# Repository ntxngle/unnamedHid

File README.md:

# unnamedHid
## What and Why

A multipurpose HID middleman based on a RP2040. Anything from rubber ducky scripts to word-to-phrase replacements are supported.

After witnessing the beautiful mistakes (happy little accidents?) that Apple's autocorrect creates, I sought to implement the same on my computer.

Eventually I realized what I was making was in fact not autocorrect but a very small and versatile HID injector: thus bearing this project.

Disclaimer: This project is only for educational and legal purpose. Do not attempt to write malicious programs or keyloggers. I am not responsible for reproductions of this project being used with malintent.

## Tuff photos

## How it works

THe entire device is based on the RP2040 MCU. The built-in PHY connects to the host computer (important for USB programming), and the PIO bitbang interface is connected to the slave device.

The practice of using the PIO as a second USB PHY is not an original nor failproof idea. This approach, taken from Adafruit's own implementation on their Feather boards, probably won't get you the USB3.0 speeds, or even 2 reliably. However, for low speed keyboards and even mice, this approach works just fine.

## BOM
|name       |footprint                                 |board name                          |quantity|
|-----------|------------------------------------------|------------------------------------|--------|
|100nF      |C_0402_1005Metric                         |C19,C8,C17,C11,C5,C6,C12,C9,C4,C7,C3|11      |
|1uF        |C_0402_1005Metric                         |C2,C13,C1,C10                       |4       |
|USBLC6-2SC6|SOT-23-6                                  |U6,U7                               |2       |
|AP2112K-3.3|SOT-23-5                                  |U3                                  |1       |
|22uF       |C_0402_1005Metric                         |C18                                 |1       |
|TPS2041B   |SOT-23-5                                  |U5                                  |1       |
|USB_A      |USB3_A_Receptacle_Wuerth_692122030100     |J2                                  |1       |
|R          |R_0402_1005Metric                         |R2,R1                               |2       |
|BOOT       |SW_SPST_TS-1088-xR025                     |SW1                                 |1       |
|1k         |R_0402_1005Metric                         |R7,R3,R4                            |3       |
|15k        |R_0402_1005Metric                         |R9,R8                               |2       |
|RUN        |SW_SPST_TS-1088-xR025                     |SW2                                 |1       |
|10k        |R_0402_1005Metric                         |R6,R5                               |2       |
|USB_A      |USB3_A_Plug_Wuerth_692112030100_Horizontal|J1                                  |1       |
|W25Q32JVSS |SOIC-8_5.3x5.3mm_P1.27mm                  |U4                                  |1       |
|15pF       |C_0402_1005Metric                         |C15,C16                             |2       |
|ABM8-272-T3|Crystal_SMD_3225-4Pin_3.2x2.5mm           |Y1                                  |1       |
|RP2040     |QFN-56-1EP_7x7mm_P0.4mm_EP3.2x3.2mm       |U1                                  |1       |

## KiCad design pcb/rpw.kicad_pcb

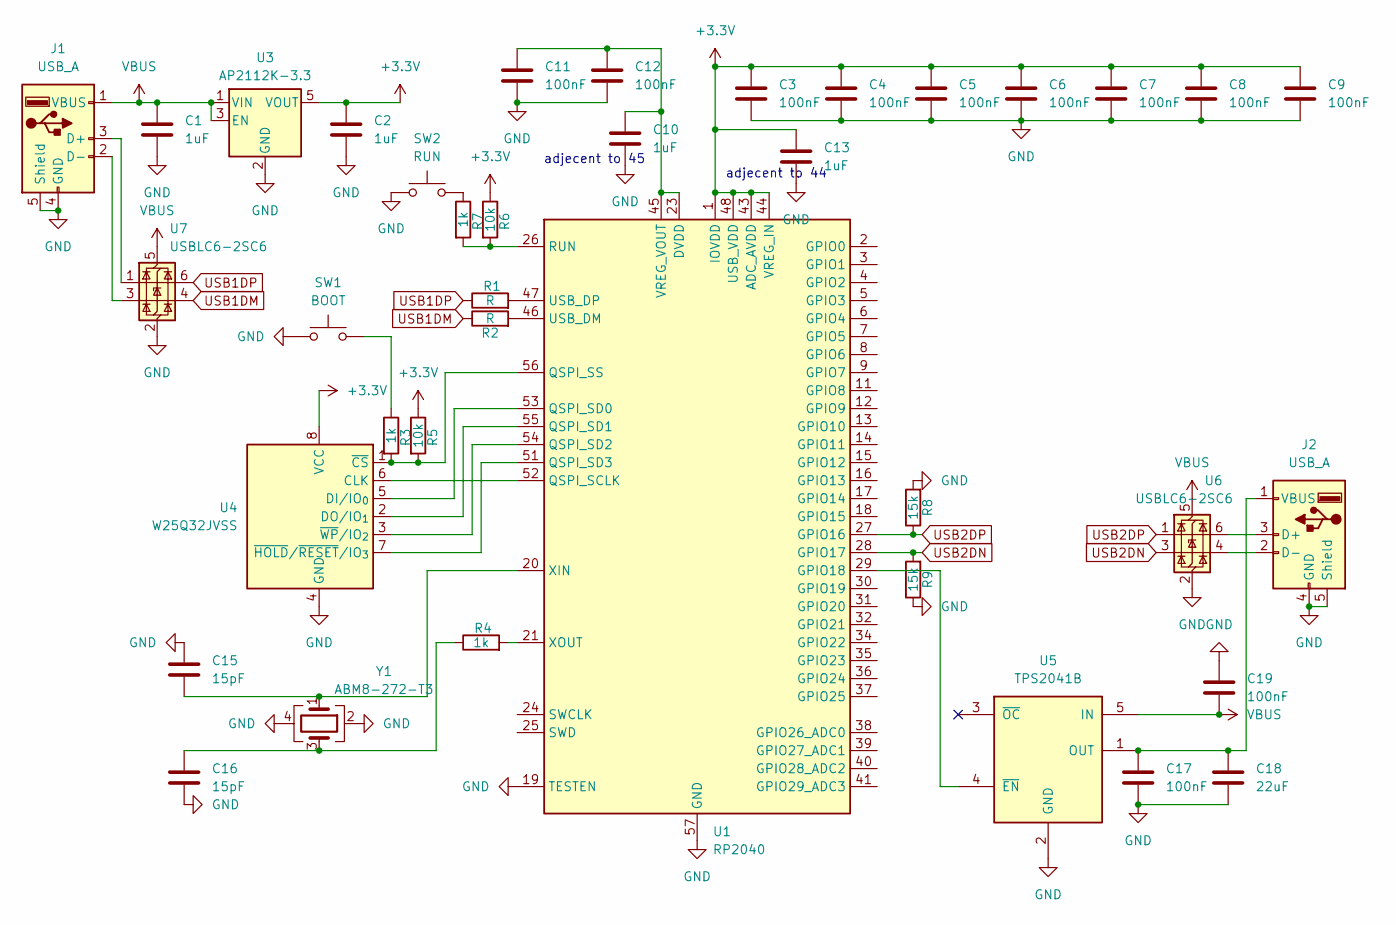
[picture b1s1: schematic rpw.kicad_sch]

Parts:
C1, C2, C10, C13: 1uF; C_0402_1005Metric
C3, C4, C5, C6, C7, C8, C9, C11, C12, C17, C19: 100nF; C_0402_1005Metric
C15, C16: 15pF; C_0402_1005Metric
C18: 22uF; C_0402_1005Metric
J1: USB_A; USB3_A_Plug_Wuerth_692112030100_Horizontal
J2: USB_A; USB3_A_Receptacle_Wuerth_692122030100
R1, R2: R; R_0402_1005Metric
R3, R4, R7: 1k; R_0402_1005Metric
R5, R6: 10k; R_0402_1005Metric
R8, R9: 15k; R_0402_1005Metric
SW1: BOOT; SW_SPST_TS-1088-xR025
SW2: RUN; SW_SPST_TS-1088-xR025
U1: RP2040; QFN-56-1EP_7x7mm_P0.4mm_EP3.2x3.2mm
U3: AP2112K-3.3; SOT-23-5
U4: W25Q32JVSS; SOIC-8_5.3x5.3mm_P1.27mm
U5: TPS2041B; SOT-23-5
U6, U7: USBLC6-2SC6; SOT-23-6
Y1: ABM8-272-T3; Crystal_SMD_3225-4Pin_3.2x2.5mm

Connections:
+3.3V: C2.1, C3.1, C4.1, C5.1, C6.1, C7.1, C8.1, C9.1, C13.1, R5.1, R6.1, U1.1 (IOVDD), U1.10 (IOVDD), U1.22 (IOVDD), U1.33 (IOVDD), U1.42 (IOVDD), U1.43 (ADC_AVDD), U1.44 (VREG_IN), U1.48 (USB_VDD), U1.49 (IOVDD), U3.5 (VOUT), U4.8 (VCC)
GND: C1.2, C2.2, C3.2, C4.2, C5.2, C6.2, C7.2, C8.2, C9.2, C10.2, C11.2, C12.2, C13.2, C15.1, C16.2, C17.2, C18.2, C19.1, J1.4 (GND), J1.5 (Shield), J2.4 (GND), J2.5 (Shield), R8.2, R9.1, SW1.1, SW2.1, U1.19 (TESTEN), U1.57 (GND), U3.2 (GND), U4.4 (GND), U5.2 (GND), U6.2 (GND), U7.2 (GND), Y1.2, Y1.4
unnamed: C16.1, R4.1, Y1.3
unnamed: J1.3 (D+), U7.1 (I/O1)
unnamed: J1.2 (D-), U7.3 (I/O2)
unnamed: J2.3 (D+), U6.6 (I/O1)
unnamed: J2.2 (D-), U6.4 (I/O2)
unnamed: C17.1, C18.1, J2.1 (VBUS), U5.1 (OUT)
unnamed: R3.1, SW1.2
unnamed: R7.1, SW2.2
unnamed: U1.29 (GPIO18), U5.4 (~EN)
unnamed: U1.52 (QSPI_SCLK), U4.6 (CLK)
unnamed: U1.53 (QSPI_SD0), U4.5 (DI/IO_{0})
unnamed: U1.55 (QSPI_SD1), U4.2 (DO/IO_{1})
unnamed: U1.54 (QSPI_SD2), U4.3 (~WP/IO_{2})
unnamed: U1.51 (QSPI_SD3), U4.7 (~HOLD/~RESET/IO_{3})
unnamed: R3.2, R5.2, U1.56 (QSPI_SS), U4.1 (~CS)
unnamed: R6.2, R7.2, U1.26 (RUN)
unnamed: R2.2, U1.46 (USB_DM)
unnamed: R1.2, U1.47 (USB_DP)
unnamed: C10.1, C11.1, C12.1, U1.23 (DVDD), U1.45 (VREG_VOUT), U1.50 (DVDD)
unnamed: C15.2, U1.20 (XIN), Y1.1
unnamed: R4.2, U1.21 (XOUT)
USB1DM: R2.1, U7.4 (I/O2)
USB1DP: R1.1, U7.6 (I/O1)
USB2DN: R9.2, U1.28 (GPIO17), U6.3 (I/O2)
USB2DP: R8.1, U1.27 (GPIO16), U6.1 (I/O1)
VBUS: C1.1, C19.2, J1.1 (VBUS), U3.1 (VIN), U3.3 (EN), U5.5 (IN), U6.5 (VBUS), U7.5 (VBUS)

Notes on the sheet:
adjecent to 44
adjecent to 45

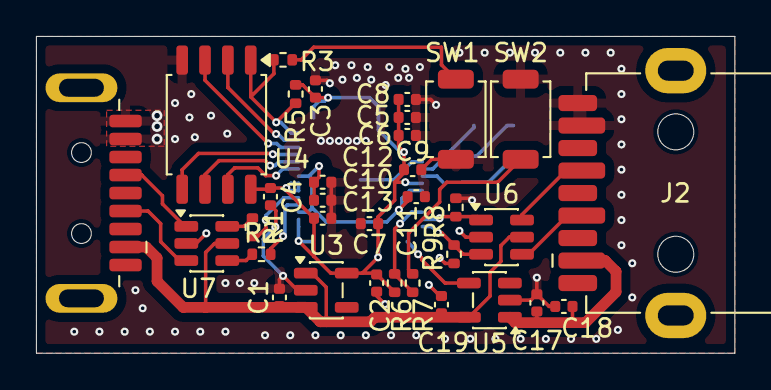
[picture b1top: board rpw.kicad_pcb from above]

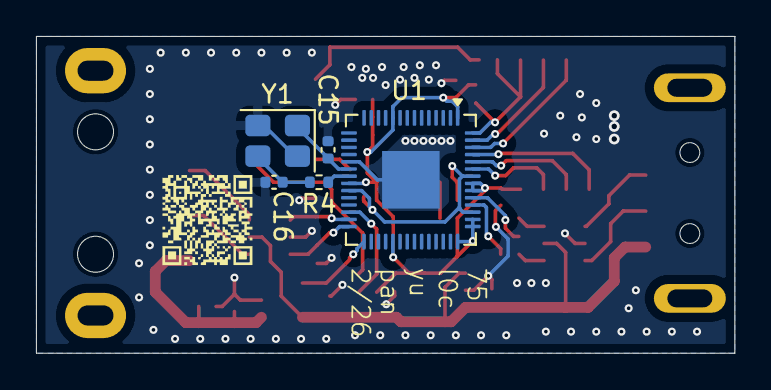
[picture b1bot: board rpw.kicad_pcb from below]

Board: 2 copper layers, 38.8 x 17.6 mm, 38 parts (5 on the bottom side), 28 nets.

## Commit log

2026-06-19 larp
